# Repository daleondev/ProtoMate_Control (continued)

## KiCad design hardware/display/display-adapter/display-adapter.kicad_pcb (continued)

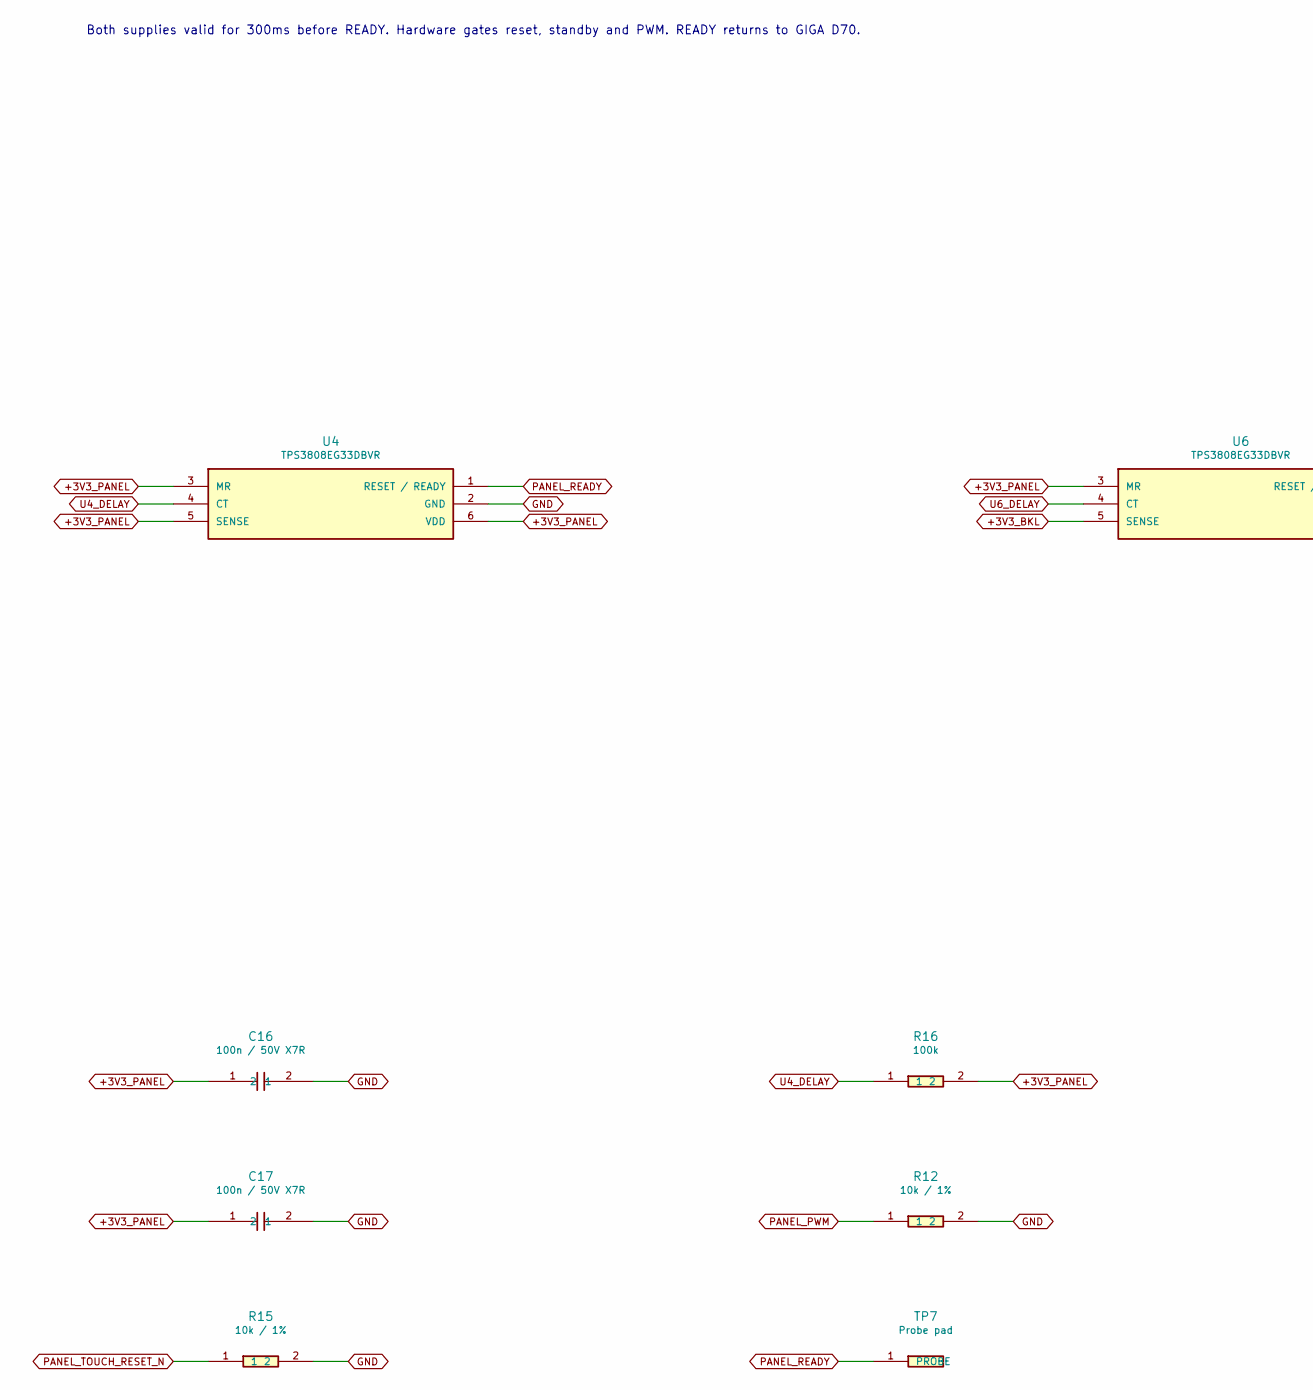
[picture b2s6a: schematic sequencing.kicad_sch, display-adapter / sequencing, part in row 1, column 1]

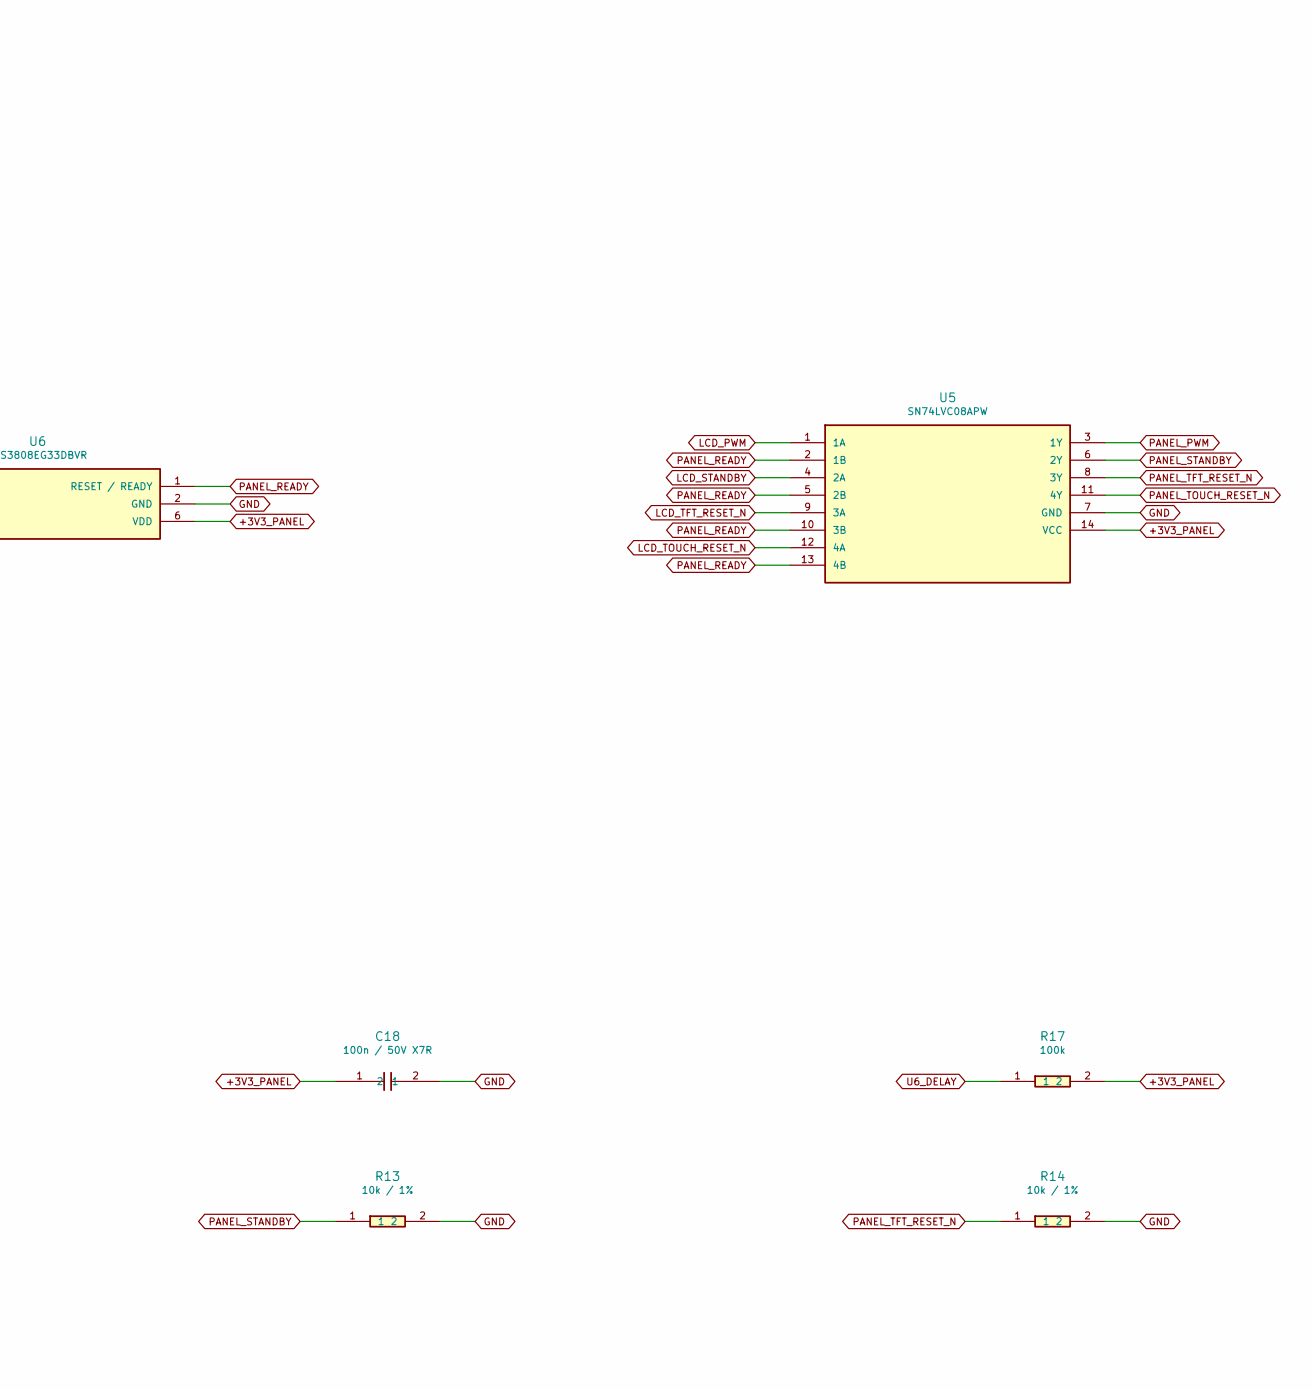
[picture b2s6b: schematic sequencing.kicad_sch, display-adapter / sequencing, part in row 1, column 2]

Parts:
C16, C17, C18: 100n / 50V X7R; C_0603_1608Metric; MPN C0603C104K5RACTU
R12, R13, R14, R15: 10k / 1%; R_0603_1608Metric; MPN RC0603FR-0710KL
R16, R17: 100k; R_0402_1005Metric; MPN RC0402FR-07100KL
TP7: Probe pad; TestPoint_1.0mm; MPN PCB copper feature
U4, U6: TPS3808EG33DBVR; SOT-23-6_UpperPin1; MPN TPS3808EG33DBVR
U5: SN74LVC08APW; TSSOP-14_4.4x5mm_P0.65mm; MPN SN74LVC08APW

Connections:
+3V3_BKL: U6.5 (SENSE); also elsewhere on the board
+3V3_PANEL: C16.1, C17.1, C18.1, R16.2, R17.2, U4.3 (MR), U4.5 (SENSE), U4.6 (VDD), U5.14 (VCC), U6.3 (MR), U6.6 (VDD); also elsewhere on the board
GND: C16.2, C17.2, C18.2, R12.2, R13.2, R14.2, R15.2, U4.2 (GND), U5.7 (GND), U6.2 (GND); also elsewhere on the board
LCD_PWM: U5.1 (1A); also elsewhere on the board
LCD_STANDBY: U5.4 (2A); also elsewhere on the board
LCD_TFT_RESET_N: U5.9 (3A); also elsewhere on the board
LCD_TOUCH_RESET_N: U5.12 (4A); also elsewhere on the board
PANEL_PWM: R12.1, U5.3 (1Y); also elsewhere on the board
PANEL_READY: TP7.1, U4.1 (RESET / READY), U5.2 (1B), U5.5 (2B), U5.10 (3B), U5.13 (4B), U6.1 (RESET / READY); also elsewhere on the board
PANEL_STANDBY: R13.1, U5.6 (2Y); also elsewhere on the board
PANEL_TFT_RESET_N: R14.1, U5.8 (3Y); also elsewhere on the board
PANEL_TOUCH_RESET_N: R15.1, U5.11 (4Y); also elsewhere on the board
U4_DELAY: R16.1, U4.4 (CT)
U6_DELAY: R17.1, U6.4 (CT)

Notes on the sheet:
Both supplies valid for 300ms before READY. Hardware gates reset, standby and PWM. READY returns to GIGA D70.

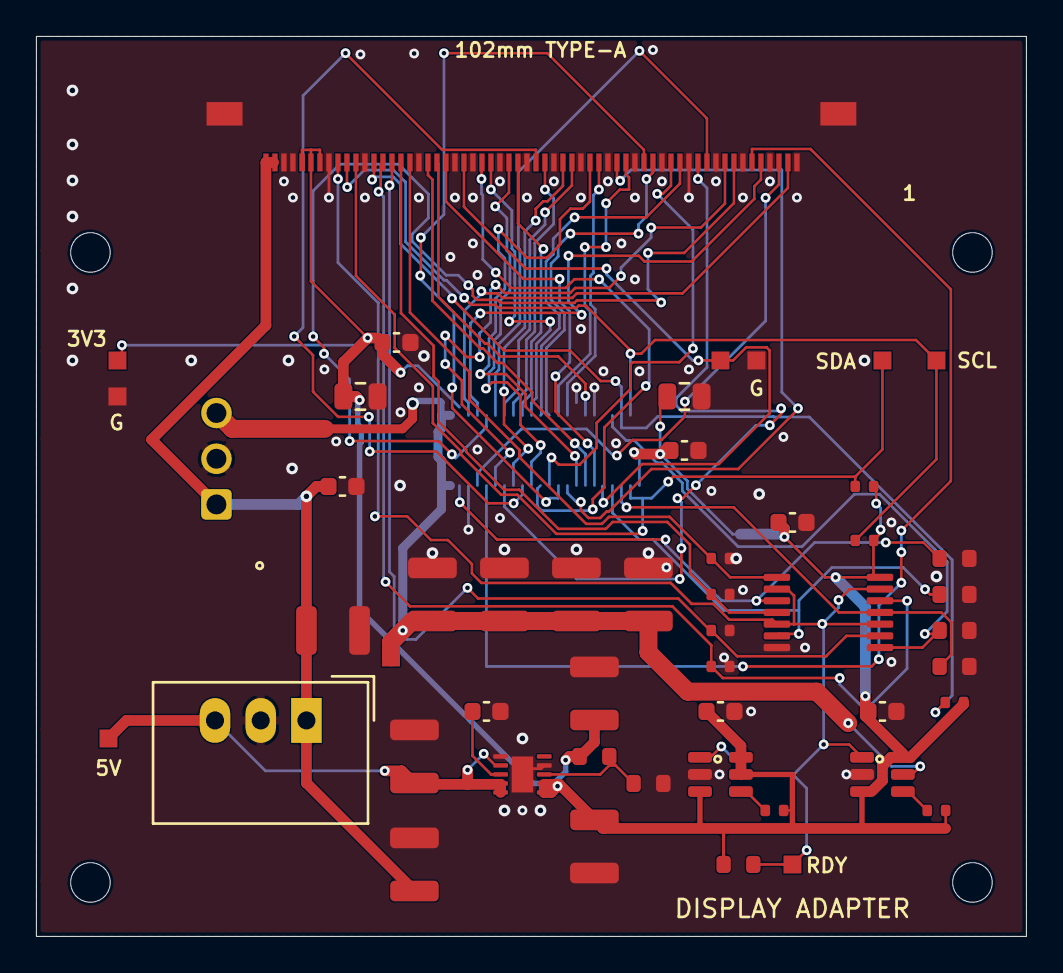
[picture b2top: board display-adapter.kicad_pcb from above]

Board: 4 copper layers, 55.0 x 50.0 mm, 55 parts (1 on the bottom side), 49 nets.

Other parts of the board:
H1, H2, H3, H4: MountingHole_2.2mm_M2

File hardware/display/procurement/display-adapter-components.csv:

Board,Revision,Designators,Installed quantity,Purchase quantity,Circuit value,PCB package,Assembly,Original BOM MPN,Purchase manufacturer,Purchase MPN,Mouser part number,Availability evidence,Indexed stock,Index age,Lookup date,Source URL,Notes
display-adapter,G,J1,1,1,DF23C-50DP-0.5V(92),DF23C-50DP-0.5V,SMT,DF23C-50DP-0.5V(92),Hirose,DF23C-50DP-0.5V(92),798-DF23C50DP05V92,stock-indexed,1575,2 weeks ago,2026-10-22,https://www.mouser.com/en/ProductDetail/Hirose-Connector/DF2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,Exact 50-pin mating plug; fit on display PCB underside.
display-adapter,G,J2,1,1,505110-6091,Molex_505110-6091_1x60_P0.50mm,SMT,505110-6091,Molex,505110-6091,538-505110-6091,stock-indexed,11530,last week,2026-10-22,https://eu.mouser.com/en/ProductDetail/Molex/505110-6091?qs=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,Two bottom-contact sockets per pair; match Molex 15018-0563 Type-A ear-tab cable.
display-adapter,G,U1,1,1,TSR 2-2433 / 3.3V 2A,Converter_DCDC_TRACO_TSR2-xxxx_THT,HAND,TSR 2-2433,TRACO Power,TSR 2-2433,495-TSR2-2433,stock-indexed,6134,3 weeks ago,2026-10-22,https://eu.mouser.com/en/ProductDetail/TRACO-Power/TSR-2-243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,3.3 V / 2 A; through-hole SIP module.
display-adapter,G,"C9, C11",2,2,10u / 50V X7R,C_1210_3225Metric,SMT,GRM32ER71H106KA12L,TAIYO YUDEN,MCJCU32MLB7106KPPDTJ,963-U32MLB7106KPPDTJ,stock-indexed,1535,2 months ago,2026-10-22,https://my.mouser.com/en/ProductDetail/TAIYO-YUDEN/MCJCU32ML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,"Replacement: 10 uF +/-10%, 50 V, X7R, 1210, soft termination; 2.5 +/-0.3 mm height. Original unavailable/region-restricted."
display-adapter,G,C10,1,1,100n / 50V X7R,C_0603_1608Metric,SMT,GRM188R71H104KA93D,KEMET,C0603C104K5RACTU,80-C0603C104K5R,stock-indexed,3941024,last week,2026-10-22,https://cz.mouser.com/en/ProductDetail/KEMET/C0603C104K5RACT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,"Replacement for obsolete original: 100 nF +/-10%, 50 V, X7R, 0603."
display-adapter,G,"C1, C2, C3, C4, C12, C13, C14",7,7,47u / 10V X5R,C_1210_3225Metric,SMT,GRM32ER61A476KE20L,TAIYO YUDEN,MBASL32MSB5476KPNA01,963-BASL32MSB5476KP,stock-indexed,1608,2 weeks ago,2026-10-23,https://lv.mouser.com/en/ProductDetail/TAIYO-YUDEN/MBASL32MS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,"Approved purchasing replacement: 47 uF +/-10%, 10 V, X5R, 1210; 2.5 +/-0.2 mm height. Manufacturer typical DC-bias curve gives approximately 42 uF at 3.3 V and 36 uF at 5 V, not guaranteed minima. Retain supply/ramp/load-step qualification. No footprint change."
display-adapter,G,"C5, C6",2,2,10u / 10V X5R,C_0805_2012Metric,SMT,GRM21BR61A106KE19L,KEMET,C0805C106K8PACTU,80-C0805C106K8P,stock-indexed,235800,last week,2026-10-22,https://eu.mouser.com/en/ProductDetail/KEMET/C0805C106K8PACT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,"Replacement for obsolete original: 10 uF +/-10%, 10 V, X5R, 0805; 1.25 +/-0.15 mm height."
display-adapter,G,"C7, C8, C16, C18, C17",5,5,100n / 50V X7R,C_0603_1608Metric,SMT,GRM188R71C104KA01D,KEMET,C0603C104K5RACTU,80-C0603C104K5R,stock-indexed,3941024,last week,2026-10-22,https://cz.mouser.com/en/ProductDetail/KEMET/C0603C104K5RACT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,"Replacement for EOL original: 100 nF +/-10%, X7R, 0603; voltage rating increased from 16 V to 50 V. Consolidated with display C10."
display-adapter,G,"R2, R3, R4, R5, R8",5,5,47k,R_0402_1005Metric,SMT,RC0402FR-0747KL,YAGEO,RC0402FR-0747KL,603-RC0402FR-0747KL,stock-indexed,986351,last month,2026-10-22,https://eu.mouser.com/en/ProductDetail/YAGEO/RC0402FR-0747KL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,"47 kohm, 1%, 0402."
display-adapter,G,"R6, R7",2,2,4k7,R_0402_1005Metric,SMT,RC0402FR-074K7L,YAGEO,RC0402FR-074K7L,603-RC0402FR-074K7L,stock-indexed,5902658,last week,2026-10-22,https://www.mouser.com/en/ProductDetail/YAGEO/RC0402FR-074K7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,"4.7 kohm, 1%, 0402."
display-adapter,G,U2,1,1,TSR 1-2450 / 5V 1A,Converter_DCDC_TRACO_TSR-1_THT_Trimmed,HAND,TSR 1-2450,TRACO Power,TSR 1-2450,495-TSR-1-2450,stock-indexed,13356,3 weeks ago,2026-10-22,https://eu.mouser.com/en/ProductDetail/TRACO-Power/TSR-1-245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,5 V / 1 A; through-hole SIP module.
display-adapter,G,U3,1,1,TPS7A9101DSKT,WSON-10-1EP_2.5x2.5mm_P0.5mm_EP1.2x2mm,SMT,TPS7A9101DSKR,Texas Instruments,TPS7A9101DSKT,595-TPS7A9101DSKT,stock-indexed,105,3 weeks ago,2026-10-22,https://eu.mouser.com/en/ProductDetail/Texas-Instruments/TPS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,Packaging-only replacement: same DSK-10 chip/pinout; small-reel suffix T instead of R. Exposed pad must be soldered.
display-adapter,G,C15,1,1,47n / 50V X7R,C_0603_1608Metric,SMT,GRM188R71C473KA01D,TDK,C1608X7R1H473K080AA,810-C1608X7R1H473K,stock-indexed,69961,3 weeks ago,2026-10-23,https://www.mouser.com/en/ProductDetail/TDK/C1608X7R1H473K08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,"Approved purchasing replacement: 47 nF +/-10%, 50 V, X7R, 0603; same nominal specification as the unavailable KEMET selection, voltage rating exceeds released BOM 16 V. No footprint change."
display-adapter,G,R9,1,1,31.2k / 0.1%,R_0603_1608Metric,SMT,RT0603BRD0731K2L,Vishay,TNPW060331K2BEEN,71-TNPW060331K2BEEN,stock-indexed,280,last month,2026-10-22,https://www.mouser.tw/en/ProductDetail/Vishay/TNPW060331K2BE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,"Replacement: 31.2 kohm, 0.1%, 25 ppm/K, 0603. Preserve precision LDO ratio; original backordered."
display-adapter,G,R10,1,1,10k / 0.1%,R_0603_1608Metric,SMT,RT0603BRD0710KL,YAGEO,RT0603BRD0710KL,603-RT0603BRD0710KL,stock-indexed,69151,last week,2026-10-22,https://eu.mouser.com/en/ProductDetail/YAGEO/RT0603BRD0710KL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,"10 kohm, 0.1%, 25 ppm/K, 0603. Do not confuse with ordinary 1% 10 kohm."
display-adapter,G,"R11, R12, R13, R14, R15",5,5,10k / 1%,R_0603_1608Metric,SMT,RC0603FR-0710KL,YAGEO,RC0603FR-0710KL,603-RC0603FR-0710KL,stock-indexed,1640807,last week,2026-10-22,https://www.mouser.com/en/ProductDetail/YAGEO/RC0603FR-0710K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,"10 kohm, 1%, 0603."
display-adapter,G,"U4, U6",2,2,TPS3808EG33DBVR,SOT-23-6_UpperPin1,SMT,TPS3808G33DBVR,Texas Instruments,TPS3808EG33DBVR,595-TPS3808EG33DBVR,user-confirmed-orderable,4336,last week,2026-10-23,https://www.mouser.de/ProductDetail/Texas-Instruments/TPS380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,"TPS3808E functional replacement, not a packaging-only substitution: same DBV SOT-23-6 pinout, 3.07 V nominal threshold and active-low open-drain reset. Existing 100 kohm CT pull-ups retain 300 ms nominal delay (180-420 ms). 3.3 V operation is within the 1.7-6 V range; 10 kohm RESET pull-up is compatible. Lower typical quiescent current (0.6 uA). Datasheet undervoltage detect delay is 30 us typical / 50 us maximum at 5% overdrive; retain first-board brownout qualification. User confirmed regional purchase availability for the required two parts on 2026-10-23; stock quantity remains indexed, not live verified. No circuit or footprint change."
display-adapter,G,"R16, R17",2,2,100k,R_0402_1005Metric,SMT,RC0402FR-07100KL,YAGEO,RC0402FR-07100KL,603-RC0402FR-07100KL,stock-indexed,6394487,last month,2026-10-22,https://www.mouser.com/en/ProductDetail/YAGEO/RC0402FR-07100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,"100 kohm, 1%, 0402."
display-adapter,G,U5,1,1,SN74LVC08APW,TSSOP-14_4.4x5mm_P0.65mm,SMT,SN74LVC08APWR,Texas Instruments,SN74LVC08APW,595-SN74LVC08APW,stock-indexed,252,last month,2026-10-22,https://www.mouser.com/en/ProductDetail/Texas-Instruments/SN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,"Packaging-only replacement: same TSSOP-14 PW chip, supplied in tube; original reel variant backordered."

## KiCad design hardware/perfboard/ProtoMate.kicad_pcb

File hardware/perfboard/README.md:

# ProtoMate stepper perfboard

Open **[ProtoMate.kicad_pro](ProtoMate.kicad_pro)** in KiCad 10. The complete
system schematic and linked perfboard layout share the same project name and
component identities.

The controller is the **Arduino GIGA R1 WiFi / STM32H747XIH6**. Its M4
owns motor generation, feedback, reference switches and driver diagnostics.
The physical perfboard uses four cable harnesses to the GIGA; it is a separate
board, not the display shield. Controller destinations use the Arduino's
printed **D/A labels**, checked against the
[official pinout](https://docs.arduino.cc/resources/pinouts/ABX00063-full-pinout.pdf)
and the repository's current CubeMX configuration.

Power the GIGA independently through USB-C. Its **3V3 output feeds J101.8**;
ground is common with the perfboard. **Do not connect the buck's 5 V output to
GIGA 5V, VIN or USB.** The buck powers the DM542T signal interface and the
encoder's 5 V circuitry; 24 V supplies the three motor drivers.

```text
hardware/perfboard/
├── ProtoMate.kicad_pro       Project settings and electrical checks
├── ProtoMate.kicad_sch       Root sheet: controller, power, sheet navigation
├── ProtoMate.kicad_pcb       47 × 65 hole perfboard placement and hand wiring
├── sheets/                  Motor interfaces, encoder, headers, switches
├── libraries/               Project-local symbols, footprints and buck 3D model
├── sym-lib-table            Relative symbol-library registration
├── fp-lib-table             Relative footprint-library registration
├── assembly/                Build instructions, parts, hole/wire/harness tables
├── exports/                 Schematic/assembly PDFs and verification reports
└── tools/                   Repeatable checks and export command
```

## Schematic and layout relationship

The root schematic links five child sheets: M1/DM542T, M2/M3/TMC2209,
M1 encoder, perfboard cable headers, and reference limit switches.
Global net names connect these sheets electrically. The connector sheet defines
J101–J107 and J113, and the reference-switch sheet defines J108–J111.
J104 is the ten-way DM542T screw terminal for control, ALM and 24 V power.
The M1 sheet defines pull-up R30; J101 carries ALM to the GIGA. All connector pin numbers match the layout and
[harness table](assembly/Harness.csv).

All **49 perfboard footprints** have assigned library footprints and native
links to their schematic symbols. These comprise Q1–Q6, R1–R12, R20–R30,
C1–C6, U2/U3, J101–J111 and J113. R10–R12 remain on the layout and are marked DNP.

The **buck U1 and Adafruit A3/A4 modules mount directly at J103/J105/J106**.
These footprints represent their soldered mounting pins and full module
outlines. The module symbols remain excluded from separate PCB placement:
the barrel jack and four-way motor terminals remain on their modules.
J103 has four electrical contacts: 5 V output, output ground, VIN ground and
24 V input. J105/J106 each have ten JP4 control pins plus two JP1 power pins.
J104.9/10 provide the DM542T power connection and the two power-distribution
star joints. Dedicated underside supply/return branches feed each TMC module
through its local C1/C2 bulk capacitor connections. Motor winding cables
connect directly to the drivers. The GIGA, DM542T, motors and switches remain external. The buck's 63 × 27 mm body follows the supplied
STEP model; its nominal mounting grid is 5.08 mm within each pair and 50.8 mm
between pairs. Its barrel jack receives 24 V at the left edge.

J113 uses eight contacts for six signals and two shared ground returns to the GIGA: TX (PD5),
RX (PD6), M2 DIAG (PC3), M3 DIAG (PC0), M2 INDEX (PB8) and M3 INDEX (PB9). R29 is the shared UART's 1 kΩ TX
series resistor. J105/J106 pin 9 is UART, pin 7 is DIAG and pin 8 is INDEX.
Address straps are M2 MS1/MS2 = GND/GND and M3 = 3.3 V/GND. Both SPRD jumpers
stay open. Firmware configures current and 16 microsteps before enable; the
potentiometers do not set current in UART mode. See the
[UART wiring instructions](assembly/README.md#directly-mounted-tmc2209-modules).

The `.kicad_pcb` is a map for a purchased individual-pad board: F.Cu represents
top jumpers, B.Cu represents solder-side wires, and vias represent wire passages.
Use the **65 × 47-hole board**, oriented as **47 columns × 65 rows**, A1–BM47,
at 2.54 mm pitch. The outer hole centres span **116.84 × 162.56 mm**; the
nominal outline is 119.38 × 165.10 mm with half-pitch margins. J104 and both TMC modules
sit along the top edge with their cable entries facing outward. J107 sits below
J104, keeping both motor-1 cables together. J101, J113, J102 and J108 form a
left-edge GIGA connector bank with 9.1 mm gaps between bodies and pin 1 at
the bottom of every header. The encoder receiver and level converters occupy
the centre-left; the DM542T transistor stages occupy the right interior.
The buck sits at the bottom left, with the three switch cable headers at the
bottom right. Q1–Q3 have 30.48 mm between stages; Q4–Q6 have
15.24 mm between stages. Decoupling capacitors stay close to their ICs.
The barrel jack faces the left edge.
The wire schedule specifies underside routes and insulated top crossovers
through dedicated free holes. All wire ends are soldered underneath. J101's pin 1 is
at Z4; odd pins run up column 4 and even pins up column 3. The 11 designated
power connections all stay underneath and use 0.5 mm² insulated copper wire;
wire drawing width does not specify conductor size.
Use the [assembly instructions](assembly/README.md) to build it.

The STEP engine uses one 32-bit TIM2 with DMA: channels 1/3/4, all AF1,
with a 10 MHz timeline. M4's runtime uses TIM5, TIM6 samples the encoder and
TIM7 services STEP completion. The GIGA's own 16 MHz crystal provides the clock;
there is no external ST-Link clock setting or board solder-bridge change.

| Signal | Perfboard contact | GIGA label | MCU pin / function |
| --- | --- | --- | --- |
| M1 STEP | J101.1 | A7 | PA0 / TIM2_CH1 |
| M1 DIR | J101.3 | D4 | PJ8 |
| M1 ALM | J101.4 | A3 | PB1 / EXTI1 |
| M2 STEP | J101.5 | D3 | PA2 / TIM2_CH3 |
| M2 DIR | J101.7 | D6 | PD13 |
| M3 STEP | J101.9 | D2 | PA3 / TIM2_CH4 |
| M3 DIR | J101.11 | D16 | PH13 |
| Shared enable | J101.12 | D15 | PC7; HIGH = disabled |
| Logic supply | J101.8 | 3V3 | GIGA output |
| M1 encoder A | J102.1 | D7 | PB4 / TIM3_CH1 |
| M1 encoder B | J102.3 | D5 | PA7 / TIM3_CH2 |
| M1 encoder Z | J102.5 | D53 | PG7 / EXTI7 |
| M1 reference | J108.1 | D49 | PE4 / EXTI4 |
| M2 reference | J108.2 | D51 | PE5 / EXTI5 |
| M3 reference | J108.3 | D47 | PB2 / EXTI2 |
| TMC UART TX | J113.1 | D18 | PD5 / USART2_TX |
| TMC UART RX | J113.3 | D19 | PD6 / USART2_RX |
| M2 INDEX | J113.4 | D8 | PB8 / EXTI8 |
| M2 DIAG | J113.5 | A4 | PC3 / EXTI3 |
| M3 INDEX | J113.6 | D9 | PB9 / EXTI9 |
| M3 DIAG | J113.7 | A6 | PC0 / EXTI0 |

All nine controller ground returns join the GIGA's common GND. See
[Harness.csv](assembly/Harness.csv) for each return and the complete driver,
module and switch wiring. The GIGA's QSPI flash is onboard and the filesystem
uses internal flash; no external QSPI or SD wiring is part of this project.

R7's 470 Ω pull-up holds shared enable HIGH during reset. M2/M3 STEP have
10 kΩ pull-downs R8/R9; M1 STEP has a path to GND through R1 and R2. The
firmware keeps STEP LOW and enable HIGH until motion is explicitly enabled.
These physical bias paths depend on the perfboard and its GIGA logic supply
being connected.

The reference switches connect to J109/J110/J111 (M1/M2/M3), pin 1 = REF and
pin 2 = GND. COM–NC is closed when released: LOW is healthy/released; HIGH
means pressed or an open cable. The GIGA supplies internal 3.3 V pull-ups
and uses both-edge EXTI. The schematic names functional switch contacts;
check the NC pair by continuity rather than relying on connector colours.

DM542T ALM+/ALM− connect to J104.7/8. R30 pulls ALM+ to 3.3 V through 4.7 kΩ;
J101.4 returns it to A3/PB1. The normally conducting alarm is LOW when healthy
and HIGH on fault/open cable. See the
[external connection instructions](assembly/README.md#external-connections).

## Controller harness

Use four short harnesses between the GIGA and perfboard: J101 (12 contacts),
J102 (6), J108 (4), and J113 (8). Each signal appears exactly once; 3.3 V
enters only at J101.8. J101 also carries the M1 alarm signal.

The nine ground conductors have deliberate roles: three STEP returns at J101,
three encoder returns at J102, one shared switch return at J108, and two shared
UART/diagnostic returns at J113. Twist each STEP and encoder signal with its
assigned ground. Bundle the slower signals with their shared returns; keep these
short local harnesses separate from motor and 24 V cables. The ground conductors
may join at a ground bus beside the GIGA; they do not need separate GIGA GND
pins. Use a short, solid connection from that bus to GIGA GND.

Module ground contacts and address straps remain connected as required by the
modules. Motor supply current uses the dedicated power branches. Ground links
in the perfboard wire schedule are required even where cable returns are shared.

## Editing workflow

1. Open the project above, then its schematic and PCB editors. Edit electrical
   connections and component assignments in the schematic.
2. Save the schematic and use **Tools → Update PCB from Schematic (F8)**.
   Keep UUID-based association; leave **Re-link footprints to schematic symbols
   based on their reference designators** unchecked. Review the proposed changes.
3. Apply the update, then place new parts and adjust the hand-wire routes in the
   PCB editor. Use the 2.54 mm hole grid for leads and wire passages. F8 transfers
   connectivity and component changes; it does not design the new wiring routes.
4. Maintain [Wires.csv](assembly/Wires.csv) after routing changes and
   [Harness.csv](assembly/Harness.csv) after cable/connector changes. Review
   mounting details in [Parts.csv](assembly/Parts.csv). Run the refresh command
   below before using or sharing the assembly documents.

Project-local footprints preserve the actual grid spacing and Diotec E/B/C
pad identities. They resolve through `${KIPRJMOD}`, so moving or cloning the
repository does not require personal library paths. The X/Y axial resistor
patterns describe the two existing orientations of the assembly drawing.

There is no separate netlist-import step or second electrical design to maintain.
KiCad's schematic-to-board check verifies the association, footprint identity,
value, and pad connectivity in the saved project.

## Checks and exports

From the repository root:

```sh
python3 hardware/perfboard/tools/refresh.py
```

Requires KiCad 10 (`kicad-cli` and its `pcbnew` Python module), Python 3 and
Poppler's `pdfunite`. The command checks ERC, DRC **with schematic parity**,
symbol links, pad nets, the hole grid, wire endpoints/connectivity, module body
clearance, mounting contacts, dedicated power branches and harness destinations.
All 20 motor, encoder, reference and driver signal contacts are checked against
the GIGA schematic and **external/CubeMX/CubeMX.ioc by default**: MCU pin,
peripheral, M4 ownership, firmware label, input pulls/edges, UART settings and
disabled startup level. The checks also reject buck 5 V or external-storage
connections on the controller. Use `--ioc /path/to/GIGA.ioc` to select another
matching GIGA configuration. The command updates:

- [Wiring.pdf](exports/Wiring.pdf): complete six-sheet system schematic.
- [Assembly.pdf](exports/Assembly.pdf): placement, top wires, mirrored underside
  and combined overview, at actual size.
- [Holes.csv](assembly/Holes.csv) and [System_Parts.csv](assembly/System_Parts.csv):
  generated pin locations and system components, including board/external scope.
- [ERC.rpt](exports/ERC.rpt), [DRC.rpt](exports/DRC.rpt) and
  [Verification.txt](exports/Verification.txt): checks of the saved native files.

Use `python3 hardware/perfboard/tools/refresh.py --check-only` to refresh just the checks.
The tool reads the native design; it never regenerates or overwrites its
schematic or layout. Wire lengths and side choices in the assembly schedule
remain manually reviewed when routing changes. The checks validate a wiring
model, not solder joints or measured encoder-interface timing.

Manufacturing silkscreen and missing-courtyard checks are waived for this
hand-wiring map. Electrical clearance, unconnected pads, schematic parity and
local footprint-library consistency are checked. No fabrication outputs are
generated.

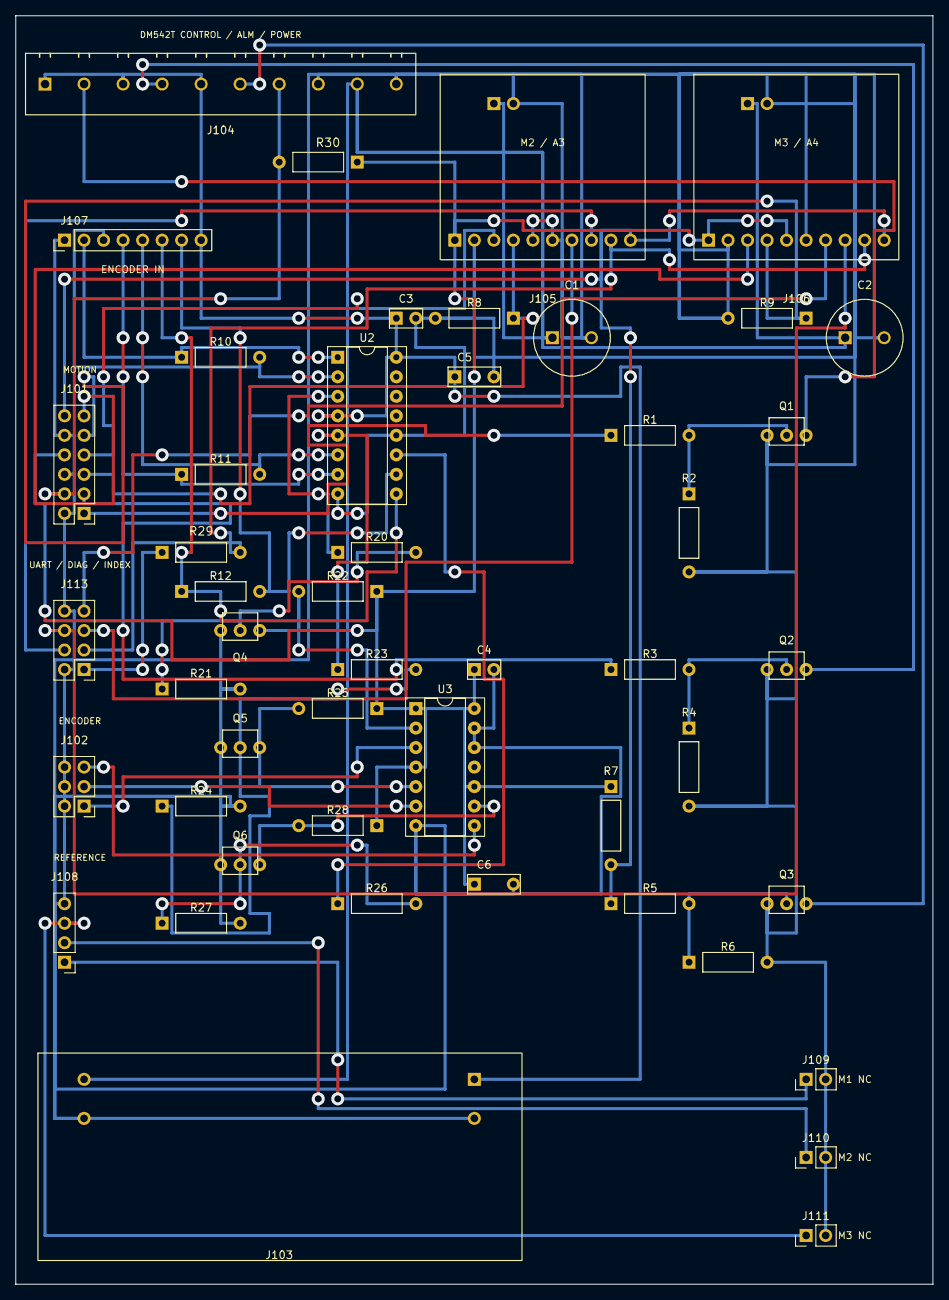
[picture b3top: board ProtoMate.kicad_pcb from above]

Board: 2 copper layers, 119.4 x 165.1 mm, 49 parts (0 on the bottom side), 45 nets.

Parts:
C1, C2: 100u / 50V; CP_Radial_D10_P5.08mm
C3, C4: 100n; C_Nonpolar_P2.54mm
C5, C6: 1u; C_Nonpolar_P5.08mm
J101: GIGA motion / 2x06; PinHeader_2x06_P2.54mm_Vertical
J102: GIGA encoder / 2x03; PinHeader_2x03_P2.54mm_Vertical
J103: U1 buck direct mount; QIQIAZI_XY3606_DirectMount
J104: DM542T control + ALM + power / screw 5.08 mm; TerminalBlock_1x10_P5.08mm_DM542T
J105: M2 TMC2209 direct mount; Adafruit_6121_JP4_Power_DirectMount
J106: M3 TMC2209 direct mount; Adafruit_6121_JP4_Power_DirectMount
J107: M1 encoder / 1x08; PinHeader_1x08_P2.54mm_Vertical
J108: GIGA references / 1x04; PinHeader_1x04_P2.54mm_Vertical
J109: M1 NC switch / 1x02; PinHeader_1x02_P2.54mm_Vertical
J110: M2 NC switch / 1x02; PinHeader_1x02_P2.54mm_Vertical
J111: M3 NC switch / 1x02; PinHeader_1x02_P2.54mm_Vertical
J113: GIGA UART / DIAG / INDEX / 2x04; PinHeader_2x04_P2.54mm_Vertical
Q1, Q2, Q3, Q4, Q5, Q6: 2N2222A; Diotec_2N2222A_EBC_P2.54mm
R1, R3, R5, R22, R25, R28, R29: 1k; R_Axial_P10.16mm_X
R2, R4: 10k; R_Axial_P10.16mm_Y
R6, R8, R9, R21, R24, R27: 10k; R_Axial_P10.16mm_X
R7: 470R; R_Axial_P10.16mm_Y
R10, R11, R12: DNP; R_Axial_P10.16mm_X
R20, R23, R26, R30: 4k7; R_Axial_P10.16mm_X
U2: AM26C32CN / DIP-16; DIP-16_W7.62mm_Socket
U3: SN74HC126N / DIP-14; DIP-14_W7.62mm_Socket

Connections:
+3V3: C4.1, C6.1, J101.8, J105.1, J106.1, J106.5, R7.1, R22.1, R25.1, R28.1, R30.1, U3.1 (1OE), U3.4 (2OE), U3.10 (3OE), U3.14 (VCC_/_3.3_V)
+5V: C3.1, C5.1, J103.1, J104.1, J104.3, J104.5, J107.8, U2.4 (G), U2.16 (VCC_/_5_V)
+24V: C1.1, C2.1, J103.4, J104.9, J105.11, J106.11
DM_DIR_N: J104.4, Q2.C
DM_ENA_N: J104.6, Q3.C
DM_PUL_N: J104.2, Q1.C
ENC_A_3V3: Q4.C, R22.2, U3.2 (1A)
ENC_A_INV5V: R20.1, U2.3 (1Y)
ENC_A_N: J107.3, R10.2, U2.2 (1A_/_A-)
ENC_A_P: J107.2, R10.1, U2.1 (1B_/_A+)
ENC_B_3V3: Q5.C, R25.2, U3.5 (2A)
ENC_B_INV5V: R23.1, U2.5 (2Y)
ENC_B_N: J107.5, R11.2, U2.6 (2A_/_B-)
ENC_B_P: J107.4, R11.1, U2.7 (2B_/_B+)
ENC_Z_3V3: Q6.C, R28.2, U3.9 (3A)
ENC_Z_INV5V: R26.1, U2.11 (3Y)
ENC_Z_N: J107.7, R12.2, U2.10 (3A_/_Z-)
ENC_Z_P: J107.6, R12.1, U2.9 (3B_/_Z+)
GND: C1.2, C2.2, C3.2, C4.2, C5.2, C6.2, J101.2, J101.6, J101.10, J102.2, J102.4, J102.6, J103.2, J103.3, J104.8, J104.10, J105.2, J105.5, J105.6, J105.12, J106.2, J106.6, J106.12, J107.1, J108.4, J109.2, J110.2, J111.2, J113.2, J113.8, Q1.E, Q2.E, Q3.E, Q4.E, Q5.E, Q6.E, R2.2, R4.2, R6.2, R8.2, R9.2, R21.2, R24.2, R27.2, U2.8 (GND), U2.12 (/G), U3.7 (GND), U3.12 (4A), U3.13 (4OE)
M1_ALM: J101.4, J104.7, R30.2
M1_DIR: J101.3, R3.1
M1_ENC_A: J102.1, U3.3 (1Y)
M1_ENC_B: J102.3, U3.6 (2Y)
M1_ENC_Z: J102.5, U3.8 (3Y)
M1_REF: J108.1, J109.1
M1_STEP: J101.1, R1.1
M2_DIAG: J105.7, J113.5
M2_DIR: J101.7, J105.3
M2_INDEX: J105.8, J113.4
M2_REF: J108.2, J110.1
M2_STEP: J101.5, J105.4, R8.1
M3_DIAG: J106.7, J113.7
M3_DIR: J101.11, J106.3
M3_INDEX: J106.8, J113.6
M3_REF: J108.3, J111.1
M3_STEP: J101.9, J106.4, R9.1
unnamed: Q1.B, R1.2, R2.1
unnamed: Q2.B, R3.2, R4.1
unnamed: Q3.B, R5.2, R6.1
unnamed: Q4.B, R20.2, R21.1
unnamed: Q5.B, R23.2, R24.1
unnamed: Q6.B, R26.2, R27.1
STEPPERS_EN_N: J101.12, J105.10, J106.10, R5.1, R7.2
TMC_UART_RX: J105.9, J106.9, J113.3, R29.2
TMC_UART_TX: J113.1, R29.1

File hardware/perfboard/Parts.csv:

References,Quantity,Part,Mounting / note
Q1 Q2 Q3 Q4 Q5 Q6,6,Diotec 2N2222A,TO-92; E1/B2/C3; 2.54 mm lead spacing
U2,1,AM26C32CN,DIP-16; 7.62 mm rows
U2 socket,1,DIP-16 socket,7.62 mm rows
U3,1,SN74HC126N,PDIP-14; 7.62 mm rows; user already owns
U3 socket,1,DIP-14 socket,7.62 mm rows; notch toward row A
R1 R3 R5 R22 R25 R28,6,1 kohm resistor,Axial 0.25 W; 10.16 mm hole spacing
R2 R4 R6 R8 R9 R21 R24 R27,8,10 kohm resistor,Axial 0.25 W; 10.16 mm hole spacing
R20 R23 R26,3,4.7 kohm resistor,Axial 0.25 W; 10.16 mm hole spacing
R7,1,470 ohm resistor,Axial 0.25 W; 10.16 mm hole spacing
R10 R11 R12,0,DNP termination resistors,Leave empty; 10.16 mm reserved hole spacing
C3 C4,2,100 nF ceramic capacitor,Nonpolar; >=16 V; 2.54 mm lead spacing
C5 C6,2,1 uF nonpolar capacitor,>=16 V; 5.08 mm lead spacing
J101,1,2x8 male header,2.54 mm pitch
J102,1,2x3 male header,2.54 mm pitch
J103,1,1x2 male header,2.54 mm pitch
J104,1,1x6 male header,2.54 mm pitch
J105 J106,2,1x10 male header,2.54 mm pitch
J107,1,1x8 male header,2.54 mm pitch
Board,1,100 x 160 mm individual-pad perfboard,2.54 mm grid; at least 60 x 36 usable holes
Wiring,As required,Insulated hookup wire and mating connectors,Signal/logic only; follow Wires.csv and Harness.csv
